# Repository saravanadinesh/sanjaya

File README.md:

# Sanjaya
KiCad design for modular sensor gateway

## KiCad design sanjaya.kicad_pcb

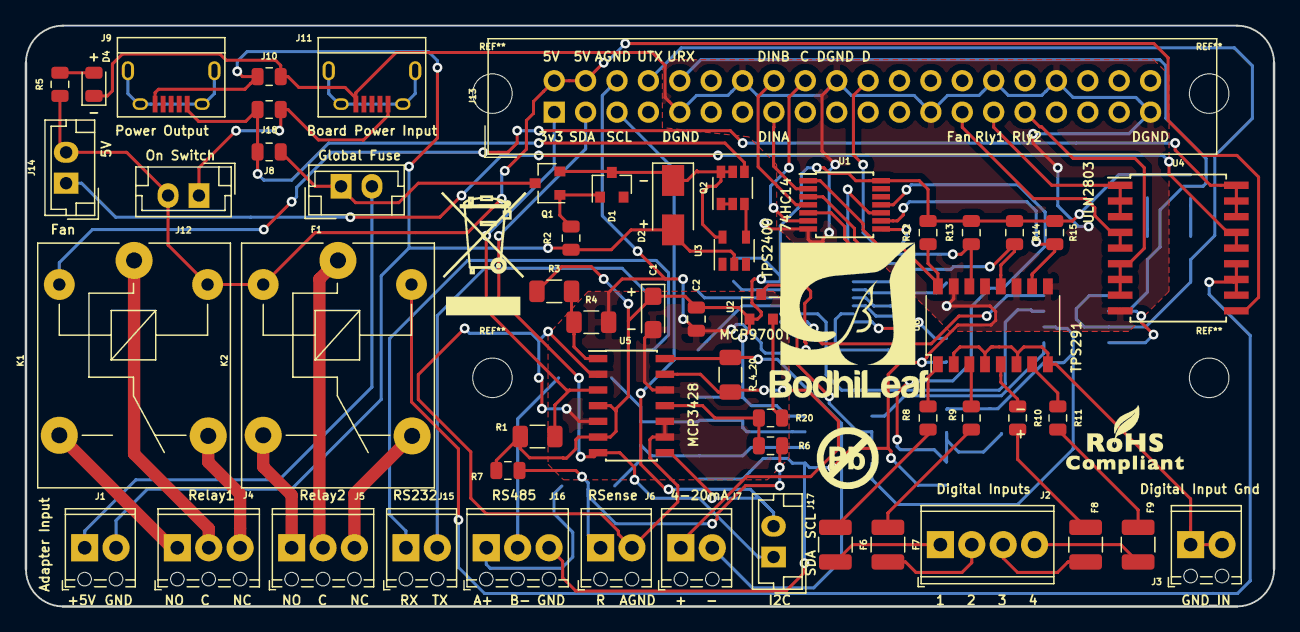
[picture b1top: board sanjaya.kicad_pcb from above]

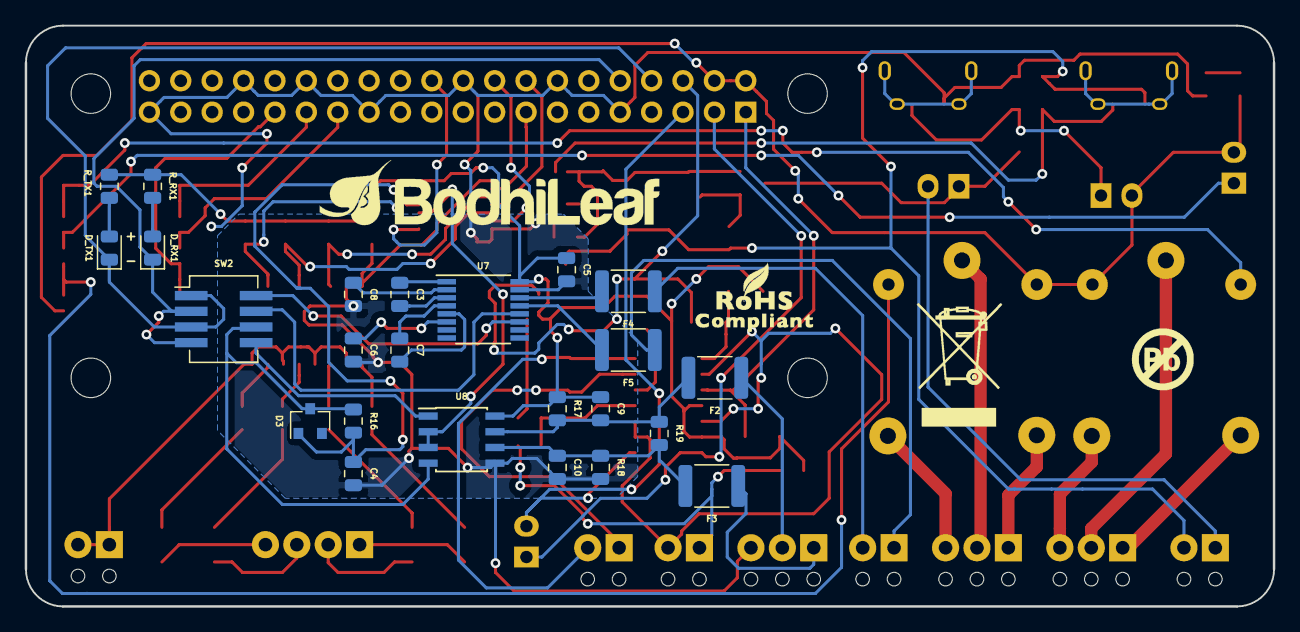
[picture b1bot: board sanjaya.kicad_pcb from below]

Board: 2 copper layers, 101.0 x 47.0 mm, 79 parts (24 on the bottom side), 80 nets.

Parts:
C1: 10uF; CP_EIA-3216-12_Kemet-S
C2, C3, C4, C5, C6, C7, C8: 0.1uF; C_0805_2012Metric
C9, C10: 1nF; C_0805_2012Metric
D1: Zener_10V; D_SOT-23_ANK
D2: Zener_24V; D_SMA
D3: MMBD914; D_SOT-23_ANK
D4: PWR_LED; LED_0805_2012Metric
D_RX1: LED; LED_0805_2012Metric
D_TX1: LED; LED_0805_2012Metric
F1: GlassFuse_3A; JST_EH_B02B-EH-A_1x02_P2.50mm_Vertical
F2, F3, F4, F5: PPTC_500mA; Fuse_1812_4532Metric
F6, F7, F8, F9: PPTC_50mA; Fuse_1210_3225Metric
J1: PWR_SUPPLY; TerminalBlock_Phoenix_MPT-0,5-2-2.54_1x02_P2.54mm_Horizontal
J2: Digital_Input_Signals; TerminalBlock_Phoenix_MPT-0,5-4-2.54_1x04_P2.54mm_Horizontal
J3: Digital_Input_Gnd; TerminalBlock_Phoenix_MPT-0,5-2-2.54_1x02_P2.54mm_Horizontal
J4, J5: Screw_Terminal_01x03; TerminalBlock_Phoenix_MPT-0,5-3-2.54_1x03_P2.54mm_Horizontal
J6: Analog_RSense; TerminalBlock_Phoenix_MPT-0,5-2-2.54_1x02_P2.54mm_Horizontal
J7: Analog_420; TerminalBlock_Phoenix_MPT-0,5-2-2.54_1x02_P2.54mm_Horizontal
J8: Supply_Safety_Bypass; R_0805_2012Metric
J9: To_PwrBank; USB_Micro-B
J10: Bat_Bak_Byp_Gnd; R_0805_2012Metric
J11: Board_PwrIn; USB_Micro-B
J12: ON_Switch; JST_EH_B02B-EH-A_1x02_P2.50mm_Vertical
J13: Raspberry_Pi_2_3; IDC-Header_2x20_P2.54mm_Vertical
J14: Fan; JST_EH_B02B-EH-A_1x02_P2.50mm_Vertical
J15: RS232; TerminalBlock_Phoenix_MPT-0,5-2-2.54_1x02_P2.54mm_Horizontal
J16: RS485; TerminalBlock_Phoenix_MPT-0,5-3-2.54_1x03_P2.54mm_Horizontal
J17: I2C; JST_EH_B02B-EH-A_1x02_P2.50mm_Vertical
J18: Bat_Bak_Byp_Vcc; R_0805_2012Metric
K1, K2: Songle-SRD; Relay_SPDT_SANYOU_SRD_Series_Form_C
Q1: Q_PMOS_GSD; SOT-23
Q2: FDC021N30; SuperSOT-6
R1: 20m; R_1206_3216Metric
R2: 10K; R_0805_2012Metric
R3, R4: 10K; R_1206_3216Metric
R5: 330; R_0805_2012Metric
R6, R20: 0Ohms; R_0805_2012Metric
R7, R8, R9, R10, R11, R12, R13, R14, R15, R16, R17, R18: 1K; R_0805_2012Metric
R19: 120; R_0805_2012Metric
R_4_20: 100; R_1206_3216Metric
R_RX1: 330; R_0805_2012Metric
R_TX1: 330; R_0805_2012Metric
SW2: SW_DIP_x04; SW_DIP_SPSTx04_Slide_KingTek_DSHP04TJ_W5.25mm_P1.27mm_JPin
U1: 74HC14; TSSOP-14_4.4x5mm_P0.65mm
U2: MCP9700T-ETT; SOT-23
U3: TPS2400BVR; SOT-23-5
U4: ULN2803A; SOIC-18W_7.5x11.6mm_P1.27mm
U5: MCP3428; SOIC-14_3.9x8.7mm_P1.27mm
U6: TLP291-4; SOP-16_4.4x10.4mm_P1.27mm
U7: MAX232; TSSOP-16_4.4x5mm_P0.65mm
U8: SN65HVD75DR; SOIC-8_3.9x4.9mm_P1.27mm

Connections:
/3V3: C1.1, C2.1, C5.1, C9.1, R1.1, R3.1, R7.1, R12.2, R13.2, R14.2, R15.2, R17.1, R_RX1.1, R_TX1.1, U1.14, U2.1, U5.4, U5.6, U7.16, U8.8
/3V3_Net+: J13.1, R1.2, U5.3
/AGND: C1.2, C2.2, J6.2, J13.6, R4.2, U2.3, U5.2, U5.5, U5.9, U5.10, U5.12
/DGND: C4.2, C5.2, C6.2, C8.2, C10.2, D4.1, J10.2, J11.5, J13.9, J13.14, J13.20, J13.25, J13.30, J13.34, J13.39, J16.3, R18.2, U1.7, U4.9, U6.9, U6.11, U6.13, U6.15, U7.15, U8.5
/D_INPUT_A: J13.15, U1.2
/D_INPUT_B: J13.16, U1.4
/D_INPUT_C: J13.18, U1.6
/D_INPUT_D: J13.22, U1.8
/actuation/Fan_Ctrl: J13.27, U4.4, U4.5
/actuation/RL1_C: J4.2, K1.1
/actuation/RL1_NC: J4.3, K1.4
/actuation/RL1_NO: J4.1, K1.3
/actuation/RL2_C: J5.2, K2.1
/actuation/RL2_NC: J5.3, K2.4
/actuation/RL2_NO: J5.1, K2.3
/actuation/Relay1_Ctrl: J13.29, U4.1, U4.2, U4.3
/actuation/Relay2_Ctrl: J13.31, U4.6, U4.7, U4.8
/analogSensing/420+: J7.1, R_4_20.2, U5.13
/analogSensing/420-: J7.2, R_4_20.1, U5.14
/analogSensing/R_Sense: J6.1, R6.2, R7.2
/analogSensing/SCL: J13.5, J17.2, U5.8
/analogSensing/SDA: J13.3, J17.1, U5.7
/analogSensing/T_Sense: R20.2, U2.2
/digitalSensing/Gnd_in: J3.1, J3.2, U6.2, U6.4, U6.6, U6.8
/digitalSensing/Vin_1: F6.2, J2.1
/digitalSensing/Vin_2: F7.2, J2.2
/digitalSensing/Vin_3: F8.2, J2.3
/digitalSensing/Vin_4: F9.2, J2.4
/powerSupply/Gnd_In: D2.2, J1.2, J9.5, J10.1, R2.2, U3.2
/powerSupply/V_adapter_out: F1.2, J1.1
/rPi/5V_In: J12.2, J13.2, J13.4, J14.2, K1.5, K2.2, R5.1, U4.10
/rPi/UART_RX: D_RX1.1, J13.10, SW2.2, SW2.4
/rPi/UART_TX: D_TX1.1, J13.8, SW2.1, SW2.3
/serial/RS232_RX: F5.1, J15.1
/serial/RS232_TX: F4.1, J15.2
/serial/RS485_A+: F3.1, J16.1
/serial/RS485_B-: F2.1, J16.2
unnamed: C3.1, U7.1
unnamed: C3.2, U7.3
unnamed: C4.1, D3.2, R16.2, U1.11
unnamed: C6.1, U7.6
unnamed: C7.1, U7.4
unnamed: C7.2, U7.5
unnamed: C8.1, U7.2
unnamed: C9.2, F2.2, R17.2, R19.1, U8.7
unnamed: C10.1, F3.2, R18.1, R19.2, U8.6
unnamed: D1.1, D2.1, Q1.2, Q2.5, Q2.6, U3.5
unnamed: D1.2, Q1.1, R2.1
unnamed: D3.1, R16.1, SW2.6, U8.4
unnamed: D4.2, R5.2
unnamed: D_RX1.2, R_RX1.2
unnamed: D_TX1.2, R_TX1.2
unnamed: F1.1, J8.2, Q1.3
unnamed: F4.2, U7.14
unnamed: F5.2, U7.13
unnamed: F6.1, R8.2
unnamed: F7.1, R9.2
unnamed: F8.1, R10.2
unnamed: F9.1, R11.2
unnamed: J11.1, J12.1, J18.1
unnamed: J14.1, U4.14, U4.15
unnamed: J8.1, J9.1, J18.2, Q2.4
unnamed: K1.2, U4.16, U4.17, U4.18
unnamed: K2.5, U4.11, U4.12, U4.13
unnamed: Q2.1, Q2.2
unnamed: Q2.3, U3.4
unnamed: R3.2, R4.1, U5.1
unnamed: R8.1, U6.1
unnamed: R9.1, U6.3
unnamed: R10.1, U6.5
unnamed: R11.1, U6.7
unnamed: R12.1, U1.1, U6.16
unnamed: R13.1, U1.3, U6.14
unnamed: R14.1, U1.5, U6.12
unnamed: R15.1, U1.9, U6.10
unnamed: R6.1, R20.1, U5.11
unnamed: SW2.5, U8.1
unnamed: SW2.7, U7.12
unnamed: SW2.8, U7.11
unnamed: U1.10, U8.2, U8.3

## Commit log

2018-09-26 First Commit. Contains: 1. Schematics empty tree except for power supply design
2018-09-29 Changes: 1. Serial (RS232, 485) circuit added.
2018-09-29 Changes: 1. Digital sensing circuit added.
2018-09-30 Changes: 1. Relay and partial analog sensing circuitry added.
2018-10-01 Changes: 1. Added Analog circuitry
2018-10-02 Changes: 1. RPi hierarchial sheet populated with appropriate circuit 2. Wiring hierarchial sheets together completed except for the temperature sensor
2018-10-02 Changes: 1. Added temperature sensor 2. Wired it to the rest of the circuit making this the first full-fledged schematic
2018-10-03 Changes: 1. Added all component footprints
2018-10-04 Changes: 1. Removed TVS diodes in favour of a RS485 transceiver of the same footprint that contains ESD protection 2. Tried different layouts.
2018-10-05 Changes: 1. Some net names, connector names changed to be more meaningful 2. I2C connector added 3. Mistake in power bank bypass connection rectified 4. Layout changed. Almost finalized.
2018-10-06 Changes: 1. Laid out the ADC part 2. Removed an unnecessary 10K resistor in the ADC voltage sense part
2018-10-07 More layout done
2018-10-11 Changes: 1. Added a power LED 2. Added PPTC to the inputs of optocoupler 3. Added PPTC to the transceiver side of the RS232 driver 4. Corrected ADC footprint
2018-10-15 Screw connectors footprint changed to 2.54mm ones and relayout done for all terminal blocks
2018-10-16 Changed USB footprints and did some more routing
2018-10-16 Some more routing done. Only 3-4 nets remaining to be routed
2018-10-16 All routing done. DRC is passing. NPTH and edge cut are the only things remaining.
2018-10-17 Changes: 1. NPTH, Edge cuts added 2. Labels for connectors added 3. DRC is passing
2018-10-17 Changes: 1. Finalized layout after adding logo, symbols, labels, polarity 2. Changed version to 0.9 on all sch files.
2018-10-18 Changes: 1. Added CE logo to the front and back of the board 2. Plotted gerber files.
2018-12-12 Changes: 1. Corrected RS485 circuit connections 2. Added silk screen labels and labels to schematics
2018-12-12 Added some more labels to schematics
